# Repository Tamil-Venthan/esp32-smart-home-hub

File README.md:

# 🏠 ESP32 Smart Home Automation Hub (Dual-Mode Cloud & Offline System)

> [!CAUTION]
> **HIGH VOLTAGE WARNING & ELECTRICAL SAFETY DISCLAIMER**  
> This project involves **110V – 240V AC Mains electricity**, which can cause fatal electrocution, severe burns, electrical arc flashes, and house fires. All hardware designs, PCB Gerbers, schematics, and firmware are provided **"AS IS" for educational and experimental research purposes only**. The authors and contributors assume **NO LIABILITY** for any injury, loss of life, fire hazard, equipment destruction, or code violations. Anyone constructing or connecting these circuits does so **entirely at their own risk**. Always turn off the main circuit breaker (MCB) before touching AC terminals, use flame-retardant enclosures, and consult a certified electrician.

An industrial-grade, production-tested **Smart Home Automation Ecosystem** supporting both **ESP32-WROOM-32** and **ESP32-S3** microcontrollers.  
Combines **free worldwide cloud control** (ESP RainMaker + Google Home + Alexa) with an **instant fallback offline web dashboard (`192.168.4.1`)**, **230V AC physical wall switch 2-way synchronization**, **DHT11 climate monitoring**, **wireless Web OTA updating**, and custom-designed **isolated dual-rail power & optocoupler PCBs**.

---

## 🌟 Key Highlights & Capabilities

* 🌍 **ESP RainMaker Cloud Backbone:** 100% free, zero-subscription worldwide control via native iOS & Android mobile apps. Zero port-forwarding or public IP configuration required.
* 🗣️ **Native Voice Assistant Integration:** Works seamlessly with **Google Assistant** and **Amazon Alexa** (*"Hey Google, turn on Light 1"*, *"Alexa, turn off the Fan"*).
* 📶 **Automated Fallback Offline Web Portal:** If Wi-Fi or mobile hotspot drops for > 10 seconds, the ESP32 automatically creates a local Wi-Fi Access Point (`SmartHome_Offline`) and serves a responsive dark-mode PWA dashboard at `http://192.168.4.1/`. Automatically switches back to cloud when Wi-Fi recovers.
* 🔄 **4-Channel 230V AC Wall Switch 2-Way Sync:** Uses Sharp **PC814** optocouplers (5,000V galvanic isolation) + 10µF zero-crossing filtering + 120ms software debounce to detect physical household wall switch flips without interference.
* ⚡ **Custom Industrial Dual-Rail Power Supply PCB:** Hi-Link **HLK-10M05** switching module delivers **+5.0V @ 2.0A** for relay coils and **+3.3V @ 1.0A** (AMS1117-3.3) for logic. Features a 2A fuse, 14D471K MOV surge clamp, 10D-9 NTC inrush limiter, 1000µF Low-ESR filter, and 2.0mm PCB creepage slot.
* 🌡️ **Comprehensive Telemetry:** Real-time ambient room temperature (°C) & humidity (% RH) via DHT11, internal ESP32 silicon die temperature, and live Wi-Fi link quality / RSSI.
* 💾 **NVS Power Outage State Recovery:** Saves relay states and custom channel names to Flash Non-Volatile Storage (`Preferences`). When mains power recovers after a blackout, appliances immediately restore their exact prior states.
* ⚡ **Wireless Web OTA Updates:** Flash new firmware wirelessly from any phone or PC browser via `http://<ESP32-IP>/update` using dual-OTA partitions (`ota_0` / `ota_1`).
* 🚀 **1-Click Flasher Tools:** Double-click automated Windows batch scripts to flash brand new ESP32 chips over USB without requiring PlatformIO, VS Code, or Python installation.

---

## 🏗️ High-Level System Architecture

```mermaid
flowchart TD
    subgraph ControlInterfaces ["User Control Interfaces"]
        App["📱 RainMaker App (iOS/Android)"]
        Voice["🗣️ Google Assistant & Alexa"]
        WebPortal["💻 Offline Web Portal (192.168.4.1)"]
        WallSwitches["🔲 4x Domestic 230V Wall Switches"]
        BootBtn["🔘 Local BOOT Button (GPIO 0)"]
    end

    subgraph CoreSystem ["ESP32 Smart Home Controller"]
        RainMaker["☁️ ESP RainMaker Engine"]
        LocalServer["🌐 Embedded WebServer (Port 80)"]
        DebounceEngine["⚡ 120ms AC Anti-Bounce Engine"]
        StateEngine["🔄 Relay State & NVS Flash Memory"]
        Telemetry["🌡️ DHT11 & Silicon Temp Telemetry"]
        
        RainMaker <--> StateEngine
        LocalServer <--> StateEngine
        WallSwitches --> DebounceEngine --> StateEngine
        BootBtn --> StateEngine
        Telemetry --> StateEngine
    end

    subgraph HardwareOutputs ["Physical Hardware Outputs"]
        RelayBoard["🔌 4-Channel 5V Relay Board"]
        Loads["💡 Lights, Ceiling Fan & Appliances"]
        StatusLED["🔵 Status Indicator LED"]
        
        StateEngine --> RelayBoard --> Loads
        StateEngine --> StatusLED
    end
```

---

## ⚡ Master Hardware Pinout Matrix

| Peripheral / Channel | ESP32-WROOM-32 Pin | ESP32-S3 DevKitC-1 Pin | Electrical Logic |
| :--- | :---: | :---: | :--- |
| 💡 **Relay 1 (Light 1)** | `GPIO 23` | `GPIO 10` | Digital Output, Active LOW |
| 💡 **Relay 2 (Light 2)** | `GPIO 22` | `GPIO 11` | Digital Output, Active LOW |
| 🌀 **Relay 3 (Fan)** | `GPIO 21` | `GPIO 12` | Digital Output, Active LOW |
| 🔌 **Relay 4 (Appliance)** | `GPIO 19` | `GPIO 13` | Digital Output, Active LOW |
| 🔲 **Wall Switch 1 (Opto)** | `GPIO 32` | `GPIO 1` | Digital Input, Internal Pull-Up, Active LOW |
| 🔲 **Wall Switch 2 (Opto)** | `GPIO 33` | `GPIO 2` | Digital Input, Internal Pull-Up, Active LOW |
| 🔲 **Wall Switch 3 (Opto)** | `GPIO 25` | `GPIO 41` | Digital Input, Internal Pull-Up, Active LOW |
| 🔲 **Wall Switch 4 (Opto)** | `GPIO 26` | `GPIO 42` | Digital Input, Internal Pull-Up, Active LOW |
| 🌡️ **DHT11 Climate Sensor** | `GPIO 4` | *(Optional)* | 1-Wire Single Bus (4.7kΩ Pull-Up) |
| 🔵 **Status LED** | `GPIO 2` (Blue LED) | `GPIO 48` (WS2812 RGB) | Solid = Online, Blink = AP / Sync |
| 🔘 **Manual BOOT Switch** | `GPIO 0` | `GPIO 0` | Momentary Pull-up (Toggles Light 1) |

---

## 📂 Repository Directory Structure

```
ESP32_Home_Automation_Repository/
│
├── agent_docs/                           <-- 🤖 Specialized AI Agent Context & Knowledge Base
│   ├── 00_AI_AGENT_README.md             <-- Master guidelines for AI assistants
│   ├── 01_SYSTEM_ARCHITECTURE.md         <-- FreeRTOS, RainMaker & WebServer blueprint
│   ├── 02_PINOUT_AND_HARDWARE_MAP.md     <-- Complete pin assignments & strapping constraints
│   ├── 03_AC_OPTOCOUPLER_LOGIC.md        <-- 230V AC zero-crossing & anti-bounce filter math
│   ├── 04_POWER_SUPPLY_SPECIFICATION.md  <-- HLK-10M05 dual supply & creepage clearance
│   ├── 05_NVS_AND_PARAM_DICTIONARY.md    <-- Preferences keys & RainMaker parameter schema
│   ├── 06_FIRMWARE_STATE_MACHINE.md      <-- Boot, Wi-Fi retry, AP mode & loop timings
│   ├── 07_TROUBLESHOOTING_MATRIX.md      <-- Root cause & fix guide for boot, brownout, Wi-Fi
│   └── 08_AGENT_PROMPT_COOKBOOK.md       <-- Copy-paste prompt templates for new features
│
├── firmware/
│   ├── esp32_wroom_production/           <-- ESP32-WROOM-32 4MB Firmware (Production Stack)
│   │   ├── src/                          <-- config.h & main.cpp
│   │   ├── bin/                          <-- Precompiled factory binaries
│   │   ├── partitions_wroom_4MB.csv      <-- Dual-OTA partition table
│   │   ├── platformio.ini                <-- Build environment
│   │   └── flash_wroom.bat               <-- 1-Click flasher
│   │
│   └── esp32_s3_16mb/                    <-- ESP32-S3 DevKitC-1 16MB Firmware
│       ├── src/                          <-- config.h & main.cpp
│       ├── bin/                          <-- Precompiled S3 binaries
│       ├── partitions_rainmaker_16MB.csv <-- 16MB partition definitions
│       ├── bootloader_dio.bin            <-- DIO mode bootloader
│       └── platformio.ini                <-- Build environment
│
├── hardware/
│   ├── 5v_power_supply_module/           <-- 220V AC to 5V/3.3V Isolated Power Supply (KiCad)
│   │   ├── 5V_Power_Supply.kicad_*       <-- KiCad schematic & PCB files
│   │   ├── 5V_Power_Supply_Schematic.pdf <-- High-res vector schematic
│   │   ├── BOM.csv                       <-- Component sourcing list
│   │   ├── production/                   <-- Gerber Zip, CPL, drill files for JLCPCB/PCBWay
│   │   └── renders/                      <-- 3D isometric PCB renders
│   │
│   ├── optocoupler_4ch_module/           <-- 4-Channel 230V AC Optocoupler Interface (KiCad)
│   │   ├── Optocoupler_4CH.kicad_*       <-- KiCad schematic & PCB files
│   │   ├── production/                   <-- Gerber Zip & JLCPCB assembly files
│   │   └── renders/                      <-- Top & Bottom PCB renders
│   │
│   └── wiring_and_pinouts/               <-- Wiring guides & electrical safety manuals
│       ├── WIRING_GUIDE_WROOM.md
│       ├── WIRING_GUIDE_S3.md
│       └── MAINS_SAFETY_CHECKLIST.md
│
├── docs/                                 <-- End-user and operational documentation
│   ├── RAINMAKER_APP_SETUP_GUIDE.md      <-- App pairing, Alexa & Google Home linking
│   ├── OFFLINE_WEB_PORTAL_GUIDE.md       <-- Using 192.168.4.1 dashboard & renaming
│   ├── OTA_UPDATE_GUIDE.md               <-- Wireless browser flashing procedure
│   └── COMPLETE_BREADBOARD_TO_PCB.md     <-- Enclosure, wiring, and manufacturing guide
│
├── tools/                                <-- Standalone 1-click batch flashing tools
│   ├── flash_esp32_wroom.bat
│   ├── flash_esp32_s3.bat
│   └── README_TOOLS.md
│
├── .gitignore                            <-- Clean git rules (preserves binaries, ignores caches)
└── LICENSE                               <-- MIT License with 230V AC Electrical Safety Disclaimer
```

---

## ⚠️ 230V AC Mains Electrical Safety & Disclaimer

1. **Lethal Voltage Hazard:** 110V–240V AC Mains power carries fatal electrocution and arc flash risks.
2. **Proper Isolation:** Never bridge or defeat the 2.0mm physical milling isolation slot on the power supply PCB. Never connect AC Mains lines directly to ESP32 low-voltage pins.
3. **Enclosure Requirement:** Always install AC power boards and optocoupler boards inside a flame-retardant ABS or polycarbonate junction box with proper strain-relief cable glands.
4. **No Liability:** The creator and contributors of this repository disclaim all liability for any personal injury, loss of life, fire, or property damage resulting from building or operating this hardware. All work on AC mains is conducted strictly at the builder's own risk.

---

## 📄 License

This project is licensed under the [**MIT License**](LICENSE) with an integrated **230V AC Mains Electrical Safety & Liability Waiver**.  
Copyright (c) 2026 Tamil-Venthan.

---

## 🚀 Quickstart: Flashing Your ESP32 in 60 Seconds

### For ESP32-WROOM-32 (Most Common):
1. Connect your ESP32-WROOM board to your PC via a micro-USB cable.
2. Navigate to `tools/` and double-click **`flash_esp32_wroom.bat`**.
3. The tool auto-detects your COM port and flashes the complete system package in under 30 seconds.
4. Follow the [RainMaker App Setup Guide](docs/RAINMAKER_APP_SETUP_GUIDE.md) to pair with your phone!

### For ESP32-S3 (16MB):
1. Connect your ESP32-S3 board to your PC via a USB-C cable.
2. Navigate to `tools/` and double-click **`flash_esp32_s3.bat`**.

---

## 🤖 For Future AI Coding Agents
If you are an AI assistant tasked with adding new features (e.g., adding an OLED display, adding PZEM-004T energy monitoring, upgrading to 8 channels, or configuring Home Assistant MQTT), read the dedicated AI manual first:  
👉 [**`agent_docs/00_AI_AGENT_README.md`**](agent_docs/00_AI_AGENT_README.md)

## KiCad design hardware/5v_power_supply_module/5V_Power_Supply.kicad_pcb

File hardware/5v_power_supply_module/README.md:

# ⚡ 220V AC to 5V (2A) & 3.3V (1A) Isolated Power Supply

Industrial-grade dual-rail power supply designed for powering ESP32 smart home systems and up to 10 relays simultaneously with zero brownout resets.

---

## 📐 Technical Specifications
* **Mains Input:** 100V – 240V AC (50/60 Hz).
* **Primary SMPS Module:** Hi-Link HLK-10M05 (5V DC @ 2.0A, 10 Watts Isolated).
* **Primary High-Current Rail:** **+5.0V @ 2.0A max** (Powers relay coils, 1000µF Low-ESR filter).
* **Secondary Logic Rail:** **+3.3V @ 1.0A max** (AMS1117-3.3 linear regulator for ESP32 & sensors).
* **Surge Protection:** 14D471K MOV (Metal Oxide Varistor, clamps surges at 710V).
* **Inrush Suppression:** 10D-9 NTC Thermistor.
* **Overcurrent Protection:** 2A 250V Slow-Blow Cartridge Fuse (5x20mm).
* **High-Voltage Creepage:** 2.0mm physical routed air gap slot (>6.3mm effective isolation).

---

## 📂 Folder Contents
* `5V_Power_Supply.kicad_pro` / `.kicad_sch` / `.kicad_pcb`: Complete KiCad project files.
* `5V_Power_Supply_Schematic.pdf`: High-resolution vector schematic for print & review.
* `BOM.csv`: Sourced bill of materials with LCSC part numbers.
* `production/`: Complete fabrication package (Gerber zip, drill files, CPL pick-and-place, and BOM).
* `renders/`: 3D PCB renders showing component placement.

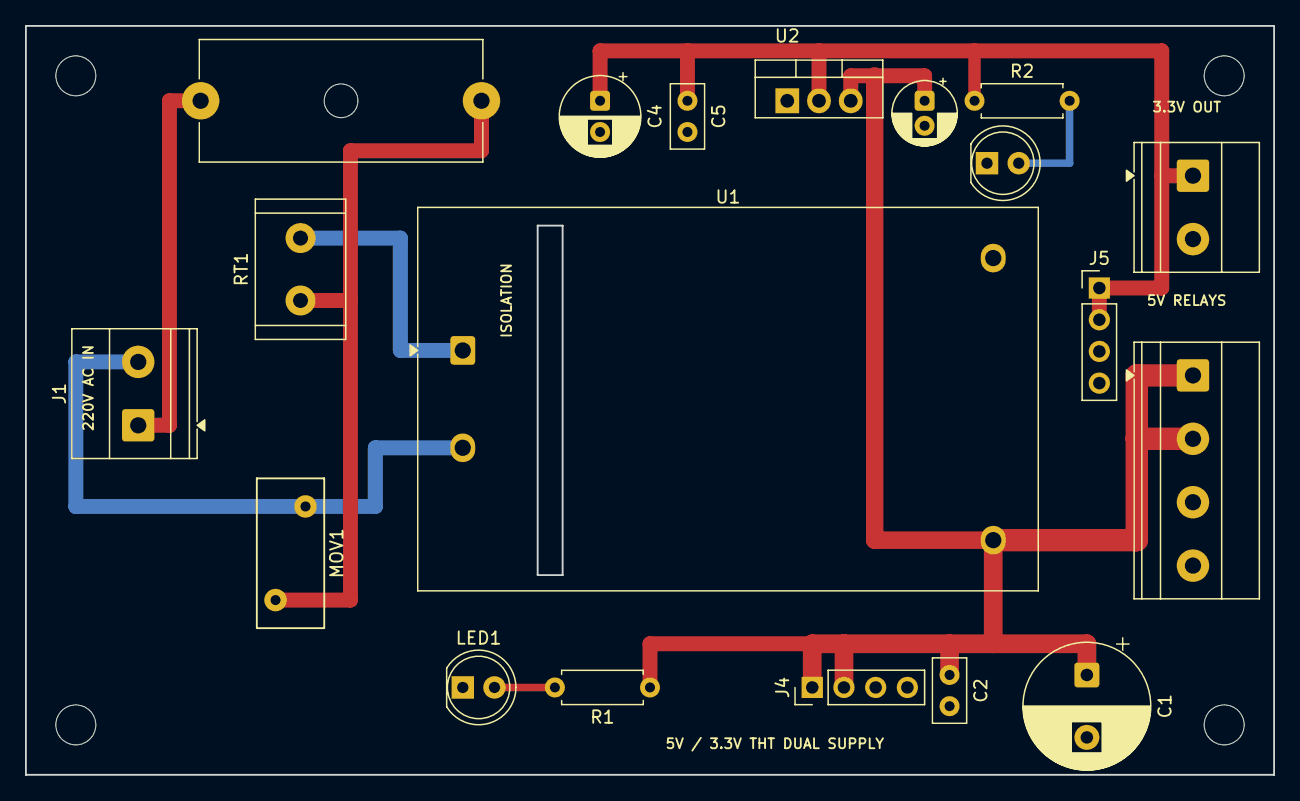
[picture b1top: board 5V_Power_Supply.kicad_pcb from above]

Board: 2 copper layers, 100.0 x 60.0 mm, 23 parts (0 on the bottom side), 9 nets.

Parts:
C1: 1000uF; CP_Radial_D10.0mm_P5.00mm
C2, C5: 100nF; C_Disc_D5.0mm_W2.5mm_P2.50mm
C3: 10uF; CP_Radial_D5.0mm_P2.00mm
C4: 100uF; CP_Radial_D6.3mm_P2.50mm
F1: 2A_250V; Fuseholder_Cylinder-5x20mm_Schurter_0031_8201_Horizontal_Op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
H1, H2, H3, H4: M3; MountingHole_3.2mm_M3
J1: 220V_AC_IN; TerminalBlock_Phoenix_MKDS-1,5-2-5.08_1x02_P5.08mm_Horizont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
J2: 5V_OUT; TerminalBlock_Phoenix_MKDS-1,5-4-5.08_1x04_P5.08mm_Horizont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
J3: 3.3V_OUT; TerminalBlock_Phoenix_MKDS-1,5-2-5.08_1x02_P5.08mm_Horizont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
J4: 5V_HDR; PinHeader_1x04_P2.54mm_Vertical
J5: 3.3V_HDR; PinHeader_1x04_P2.54mm_Vertical
LED1: 5V_OK; LED_D5.0mm
LED2: 3.3V_OK; LED_D5.0mm
MOV1: 14D471K; RV_Disc_D12mm_W5.4mm_P7.5mm
R1, R2: 1k; R_Axial_DIN0207_L6.3mm_D2.5mm_P7.62mm_Horizontal
RT1: 10D-9; R_Radial_Power_L11.0mm_W7.0mm_P5.00mm
U1: HLK-10M05; Converter_ACDC_Hi-Link_HLK-10Mxx
U2: LM1117T-3.3; TO-220-3_Vertical

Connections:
+3V3: C4.1, C5.1, J3.1, J5.1, J5.2, R2.1, U2.2
+5V: C1.1, C2.1, C3.1, J2.1, J2.2, J4.1, J4.2, R1.1, U1.4, U2.3
AC_L: F1.1, J1.1
AC_L_FUSED: F1.2, MOV1.1, RT1.1
AC_L_IN: RT1.2, U1.1
AC_N: J1.2, MOV1.2, U1.2
GND: C1.2, C2.2, C3.2, C4.2, C5.2, J2.3, J2.4, J3.2, J4.3, J4.4, J5.3, J5.4, LED1.1, LED2.1, U1.3, U2.1
unnamed: LED1.2, R1.2
unnamed: LED2.2, R2.2

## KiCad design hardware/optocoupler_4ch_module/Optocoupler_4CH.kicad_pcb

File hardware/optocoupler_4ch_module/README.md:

# ⚡ 4-Channel 230V AC Optocoupler Wall Switch Interface

Dedicated sensor interface board for connecting 4 domestic 230V AC wall switches to low-voltage 3.3V microcontrollers (ESP32-WROOM / ESP32-S3) with complete 5,000V optical galvanic isolation.

---

## 📐 Technical Specifications
* **Optocoupler IC:** 4x Sharp **PC814** (Bidirectional AC Input, DIP-4).
* **Isolation Voltage:** 5,000V RMS Galvanic Barrier.
* **Input Voltage:** 100V – 240V AC (50Hz / 60Hz) from domestic toggle or rocker switches.
* **Mains Current Draw:** ~1.15mA per channel across two 100kΩ 0.5W dropping resistors.
* **Zero-Crossing Filter:** Onboard 10µF 16V ceramic smoothing capacitors bridge the 100Hz AC zero-crossing dips, delivering continuous, jitter-free 3.3V DC logic to the ESP32.
* **Output Logic:**
  - Wall Switch **OFF** -> Output is **HIGH (3.3V)**.
  - Wall Switch **ON** -> Output is **LOW (0V / GND)**.

---

## 📂 Folder Contents
* `Optocoupler_4CH.kicad_pro` / `.kicad_sch` / `.kicad_pcb`: Complete KiCad project files.
* `production/`: JLCPCB fabrication zip (`Optocoupler_4CH_Gerbers.zip`), CPL, and BOM.
* `renders/`: High-resolution top and bottom board renders.

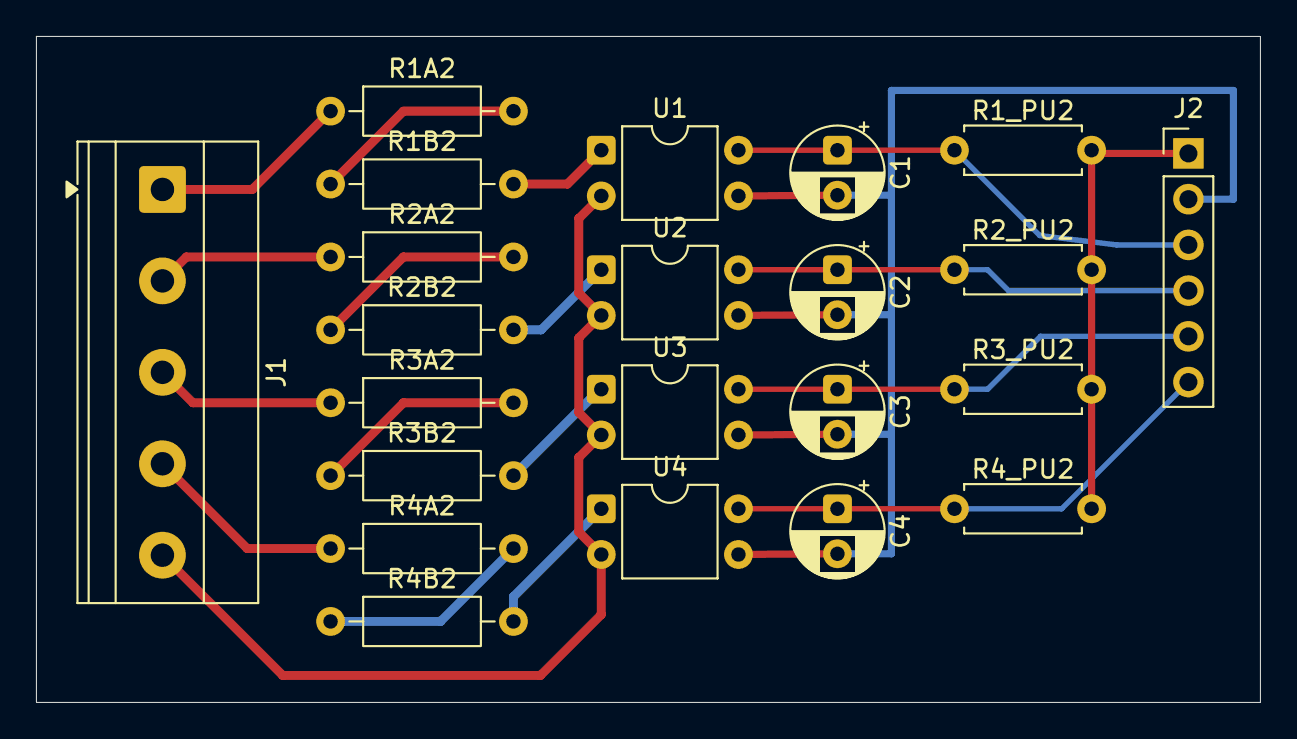
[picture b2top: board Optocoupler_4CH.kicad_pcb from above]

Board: 2 copper layers, 68.0 x 37.0 mm, 22 parts (0 on the bottom side), 19 nets.

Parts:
C1, C2, C3, C4: 10uF; CP_Radial_D5.0mm_P2.50mm
J1: AC_MAINS_INPUT; TerminalBlock_Phoenix_MKDS-1,5-5-5.08_1x05_P5.08mm_Horizont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
J2: ESP32_INTERFACE; PinHeader_1x06_P2.54mm_Vertical
R1A2, R1B2, R2A2, R2B2, R3A2, R3B2, R4A2, R4B2: 100k_0.5W; R_Axial_DIN0207_L6.3mm_D2.5mm_P10.16mm_Horizontal
R1_PU2, R2_PU2, R3_PU2, R4_PU2: 10k; R_Axial_DIN0207_L6.3mm_D2.5mm_P7.62mm_Horizontal
U1, U2, U3, U4: PC814; DIP-4_W7.62mm

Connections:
+3V3: J2.1, R1_PU2.2, R2_PU2.2, R3_PU2.2, R4_PU2.2
/AC_N: J1.5, U1.2, U2.2, U3.2, U4.2
/OUT1: C1.1, J2.3, R1_PU2.1, U1.4 (C)
/OUT2: C2.1, J2.4, R2_PU2.1, U2.4 (C)
/OUT3: C3.1, J2.5, R3_PU2.1, U3.4 (C)
/OUT4: C4.1, J2.6, R4_PU2.1, U4.4 (C)
/SW1: J1.1, R1A2.1
/SW2: J1.2, R2A2.1
/SW3: J1.3, R3A2.1
/SW4: J1.4, R4A2.1
GND: C1.2, C2.2, C3.2, C4.2, J2.2, U1.3 (E), U2.3 (E), U3.3 (E), U4.3 (E)
unnamed: R1A2.2, R1B2.1
unnamed: R1B2.2, U1.1
unnamed: R2A2.2, R2B2.1
unnamed: R2B2.2, U2.1
unnamed: R3A2.2, R3B2.1
unnamed: R3B2.2, U3.1
unnamed: R4A2.2, R4B2.1
unnamed: R4B2.2, U4.1
